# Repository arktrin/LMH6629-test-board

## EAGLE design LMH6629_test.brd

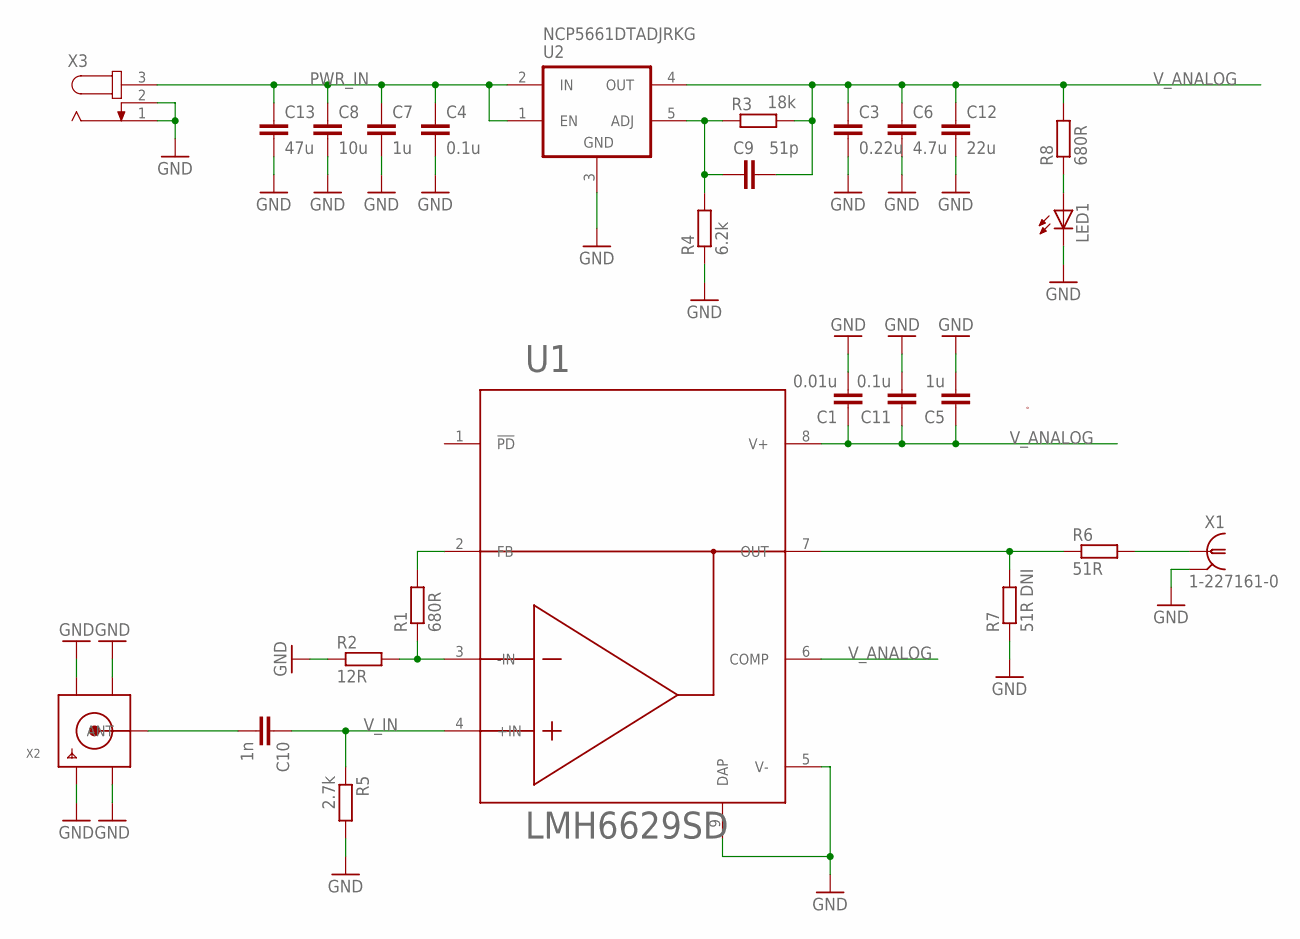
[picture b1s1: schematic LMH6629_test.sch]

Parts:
C1: 0.01u; C0603
C3: 0.22u; C0603
C4, C11: 0.1u; C0603
C5, C7: 1u; C0603
C6: 4.7u; C0805
C8: 10u; C0805
C9: 51p; C0603
C10: 1n; C0603
C12: 22u; C0805
C13: 47u; C1210
LED1: LEDCHIPLED_0603; CHIPLED_0603
R1: 680R; R0402
R2: 12R; R0402
R3: 18k; R0603
R4: 6.2k; R0603
R5: 2.7k; R0603
R6: 51R; R0603
R7: 51R DNI; R0603
R8: 680R; R0603
U1: LMH6629SD; SON50P300X300X100-9N
U2: NCP5661DTADJRKG; DPAK-5
X1: 1-227161-0; AMP_227161
X2: SMACONNECTOR_EDGE; SMA_EDGELAUNCH
X3: JACK-PLUG1; SPC4078

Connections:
-IN: R1.1, R2.2, U1.3 (-IN)
ADJ: C9.1, R3.1, R4.2, U2.5 (ADJ)
FB: R1.2, U1.2 (FB)
GND: C1.2, C3.2, C4.2, C5.2, C6.2, C7.2, C8.2, C11.2, C12.2, C13.2, LED1.C, R2.1, R4.1, R5.2, R7.1, U1.5 (V-), U1.9 (DAP), U2.3 (GND), X1.2, X2.GND@1 (GND4), X2.GND@2 (GND3), X2.GND@3 (GND2), X2.GND@4 (GND1), X3.1, X3.2
unnamed: LED1.A, R8.1
unnamed: C10.2, X2.P (ANT)
OUT: R6.2, X1.1
PWR_IN: C4.1, C7.1, C8.1, C13.1, U2.1 (EN), U2.2 (IN), X3.3
V_ANALOG: C1.1, C3.1, C5.1, C6.1, C9.2, C11.1, C12.1, R3.2, R8.2, U1.6 (COMP), U1.8 (V+), U2.4 (OUT)
V_IN: C10.1, R5.1, U1.4 (+IN)
V_OUT: R6.1, R7.2, U1.7 (OUT)

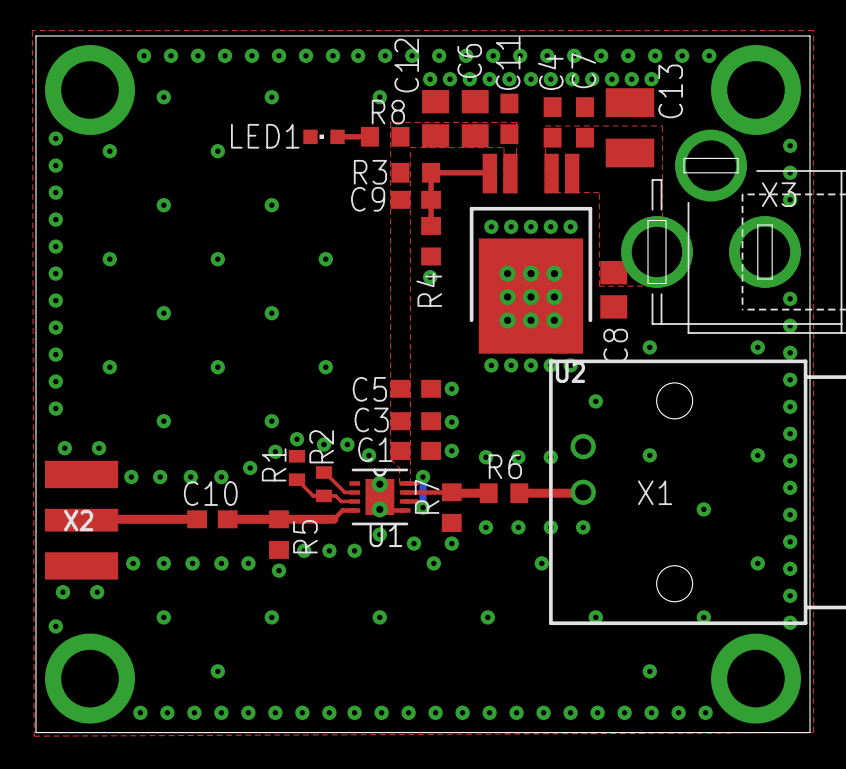
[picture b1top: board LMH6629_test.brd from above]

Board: 2 copper layers, 43.0 x 38.7 mm, 26 parts (0 on the bottom side), 11 nets.

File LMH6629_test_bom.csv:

"Part";"Value";"Device";"Package";"Description";"MF";"MPN";"OC_FARNELL";"OC_NEWARK";
"C1";"0.01u";"C-EUC0603";"C0603";"CAPACITOR, European symbol";"";"";"";"";
"C3";"0.22u";"C-EUC0603";"C0603";"CAPACITOR, European symbol";"";"";"";"";
"C4";"0.1u";"C-EUC0603";"C0603";"CAPACITOR, European symbol";"";"";"";"";
"C5";"1u";"C-EUC0603";"C0603";"CAPACITOR, European symbol";"";"";"";"";
"C6";"4.7u";"C-EUC0805";"C0805";"CAPACITOR, European symbol";"";"";"";"";
"C7";"1u";"C-EUC0603";"C0603";"CAPACITOR, European symbol";"";"";"";"";
"C8";"10u";"C-EUC0805";"C0805";"CAPACITOR, European symbol";"";"";"";"";
"C9";"51p";"C-EUC0603";"C0603";"CAPACITOR, European symbol";"";"";"";"";
"C10";"1n";"C-EUC0603";"C0603";"CAPACITOR, European symbol";"";"";"";"";
"C11";"0.1u";"C-EUC0603";"C0603";"CAPACITOR, European symbol";"";"";"";"";
"C12";"22u";"C-EUC0805";"C0805";"CAPACITOR, European symbol";"";"";"";"";
"C13";"47u";"C-EUC1210";"C1210";"CAPACITOR, European symbol";"";"";"";"";
"LED1";"";"LEDCHIPLED_0603";"CHIPLED_0603";"LED";"";"";"";"";
"R1";"680R";"R-EU_R0402";"R0402";"RESISTOR, European symbol";"";"";"";"";
"R2";"12R";"R-EU_R0402";"R0402";"RESISTOR, European symbol";"";"";"";"";
"R3";"18k";"R-EU_R0603";"R0603";"RESISTOR, European symbol";"";"";"";"";
"R4";"6.2k";"R-EU_R0603";"R0603";"RESISTOR, European symbol";"";"";"";"";
"R5";"2.7k";"R-EU_R0603";"R0603";"RESISTOR, European symbol";"";"";"";"";
"R6";"51R";"R-EU_R0603";"R0603";"RESISTOR, European symbol";"";"";"";"";
"R7";"51R DNI";"R-EU_R0603";"R0603";"RESISTOR, European symbol";"";"";"";"";
"R8";"680R";"R-EU_R0603";"R0603";"RESISTOR, European symbol";"";"";"";"";
"U1";"LMH6629SD";"LMH6629SD";"SON50P300X300X100-9N";"";"";"";"";"";
"U2";"NCP5661DTADJRKG";"NCP5661DTADJRKG";"DPAK-5";"";"";"";"";"";
"X1";"1-227161-0";"1-227161-0";"AMP_227161";"JACK,  RIGHT ANGLE, 50 OHM, PCB, BNC";"TYCO ELECTRONICS";"1-227161";"unknown";"33B3200";
"X2";"";"SMACONNECTOR_EDGE";"SMA_EDGELAUNCH";"SMA Connector";"";"";"";"";
"X3";"";"JACK-PLUG1";"SPC4078";"DC POWER JACK";"";"";"unknown";"unknown";

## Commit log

2017-10-04 init
2017-10-07 add NCP5661
2017-11-23 some progress on pcb
2017-11-24 more progress on pcb
2017-11-24 replace LDO on pcb
2017-11-26 almost done with pcb
2017-11-26 all done
2017-12-05 gerber update
2017-12-11 add BOM list

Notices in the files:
parts and their libraries:
on-semi: Copyright (C) 2008, Bob Starr
